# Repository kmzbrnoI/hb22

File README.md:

HB22
====

DCC signal booster

## Features

* Input voltage: track+1V – 35 V **DC**
* Output voltage: 14–25 V DCC
* Maximum output current: 3 A
* Adjustable output voltage
* Stepdown for stabilization (energy-effective)
* No big cooler needed
* Analog current limitation to 3 A
* DCC skew rate limitation
* RailCom support
* Possibility to connect expansion module for integration with railroad-control system
* Current sensing, voltage sensing, temperature sensing
* Short-circuit detection, (configurable) automatic restore after short-circuit

## Available expansion modules

- [MTBbus expansion module](exp-mtb)

## Principles

Main MCU does all safety-critical operations:

* Detection of short-circuit
* Railcom pause insertion

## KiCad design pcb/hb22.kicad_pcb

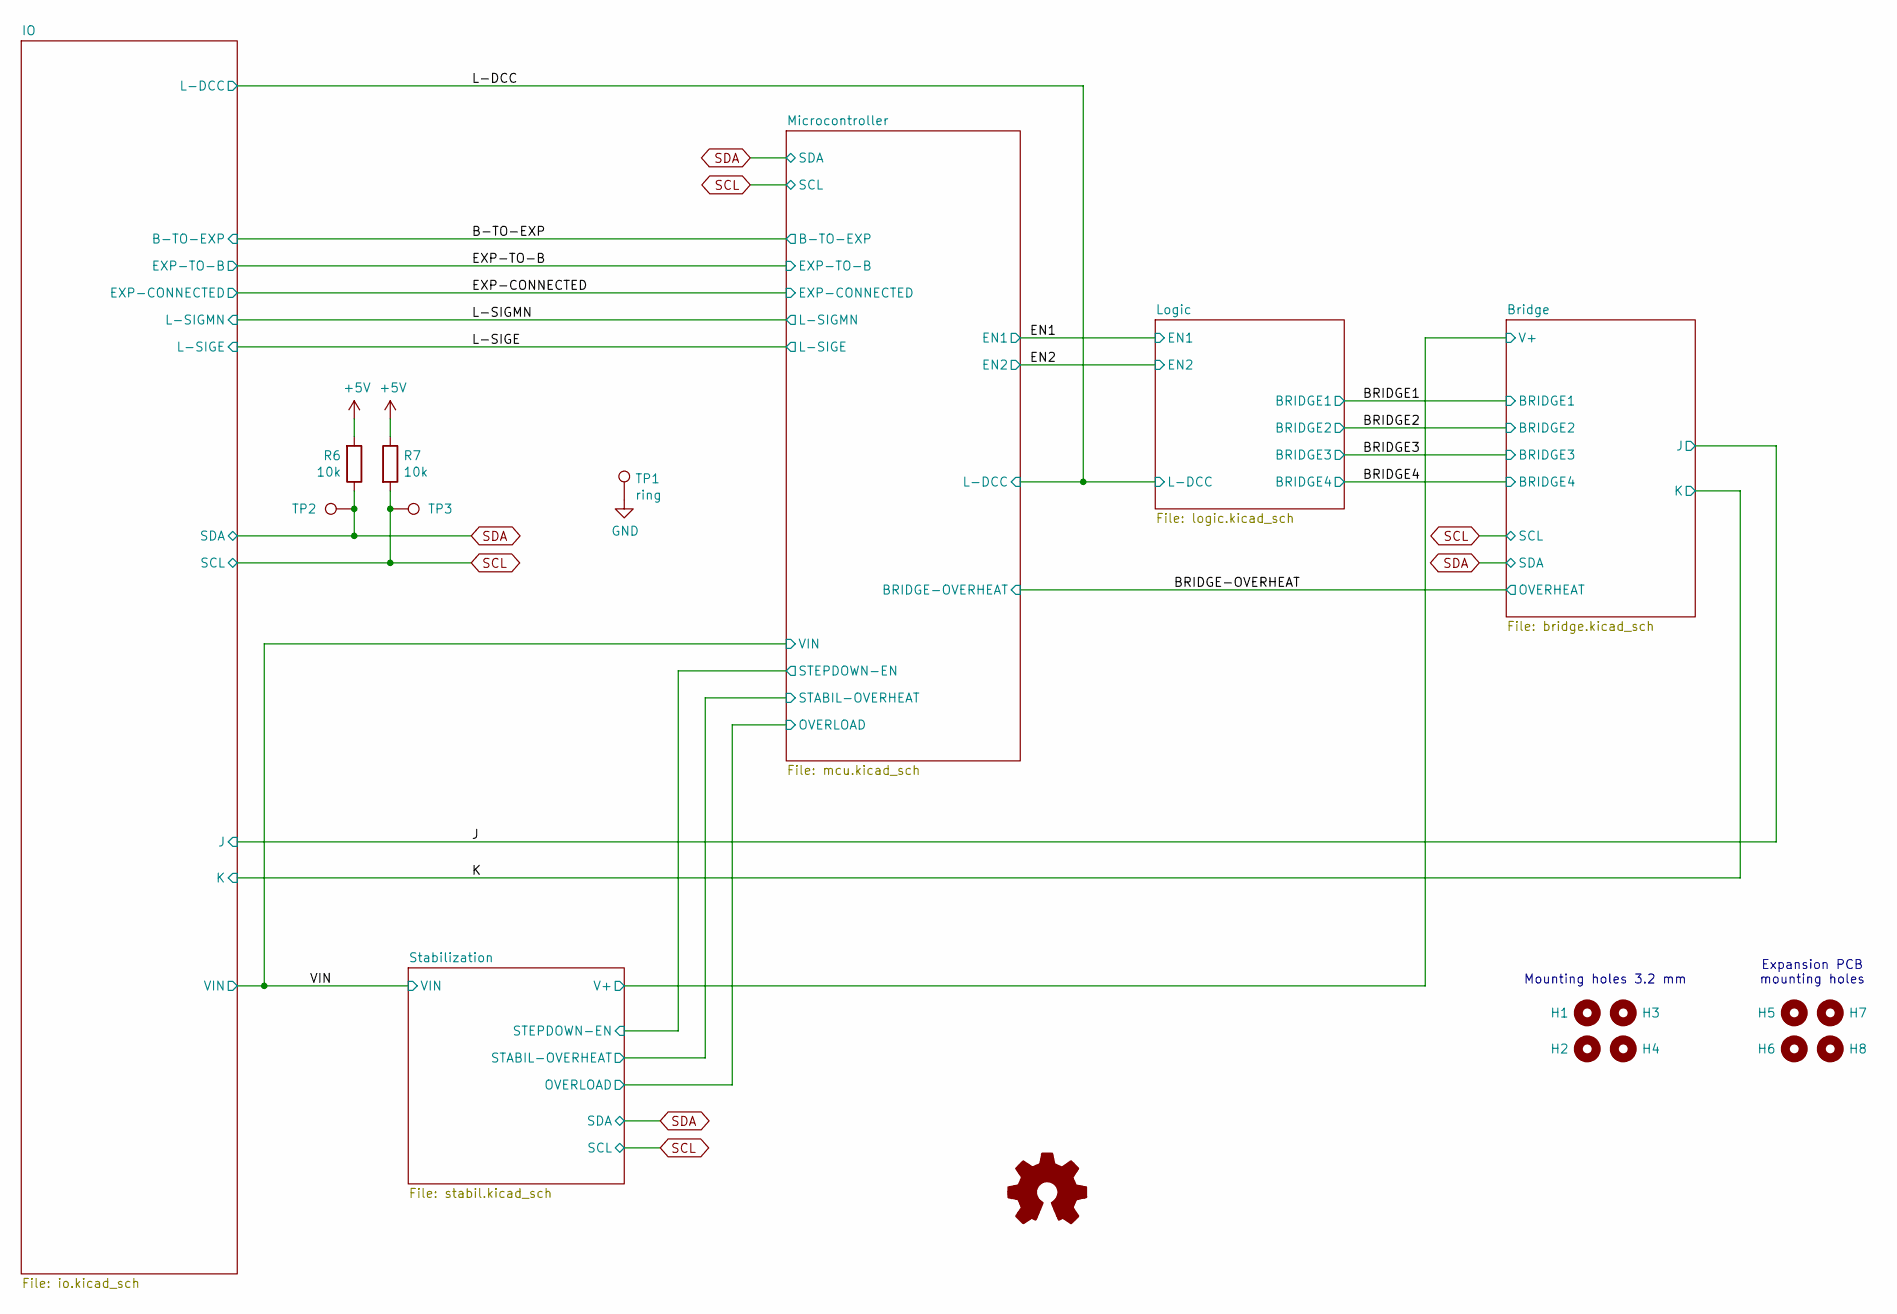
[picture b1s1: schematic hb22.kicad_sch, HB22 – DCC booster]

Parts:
H1, H2, H3, H4, H5, H6, H7, H8: MountingHole_3.2mm_M3_Pad
R6, R7: 10k; R_0805_2012Metric; LCSC C17414
TP1: ring; TestPoint_Loop_D1.80mm_Drill1.0mm_Beaded
TP2, TP3: TestPoint; TestPoint_Pad_D1.0mm

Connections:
+5V: R6.2, R7.1; also elsewhere on the board
GND: TP1.1; also elsewhere on the board
SCL: R7.2, TP3.1; also elsewhere on the board
SDA: R6.1, TP2.1; also elsewhere on the board

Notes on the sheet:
Mounting holes 3.2 mm
Expansion PCB mounting holes

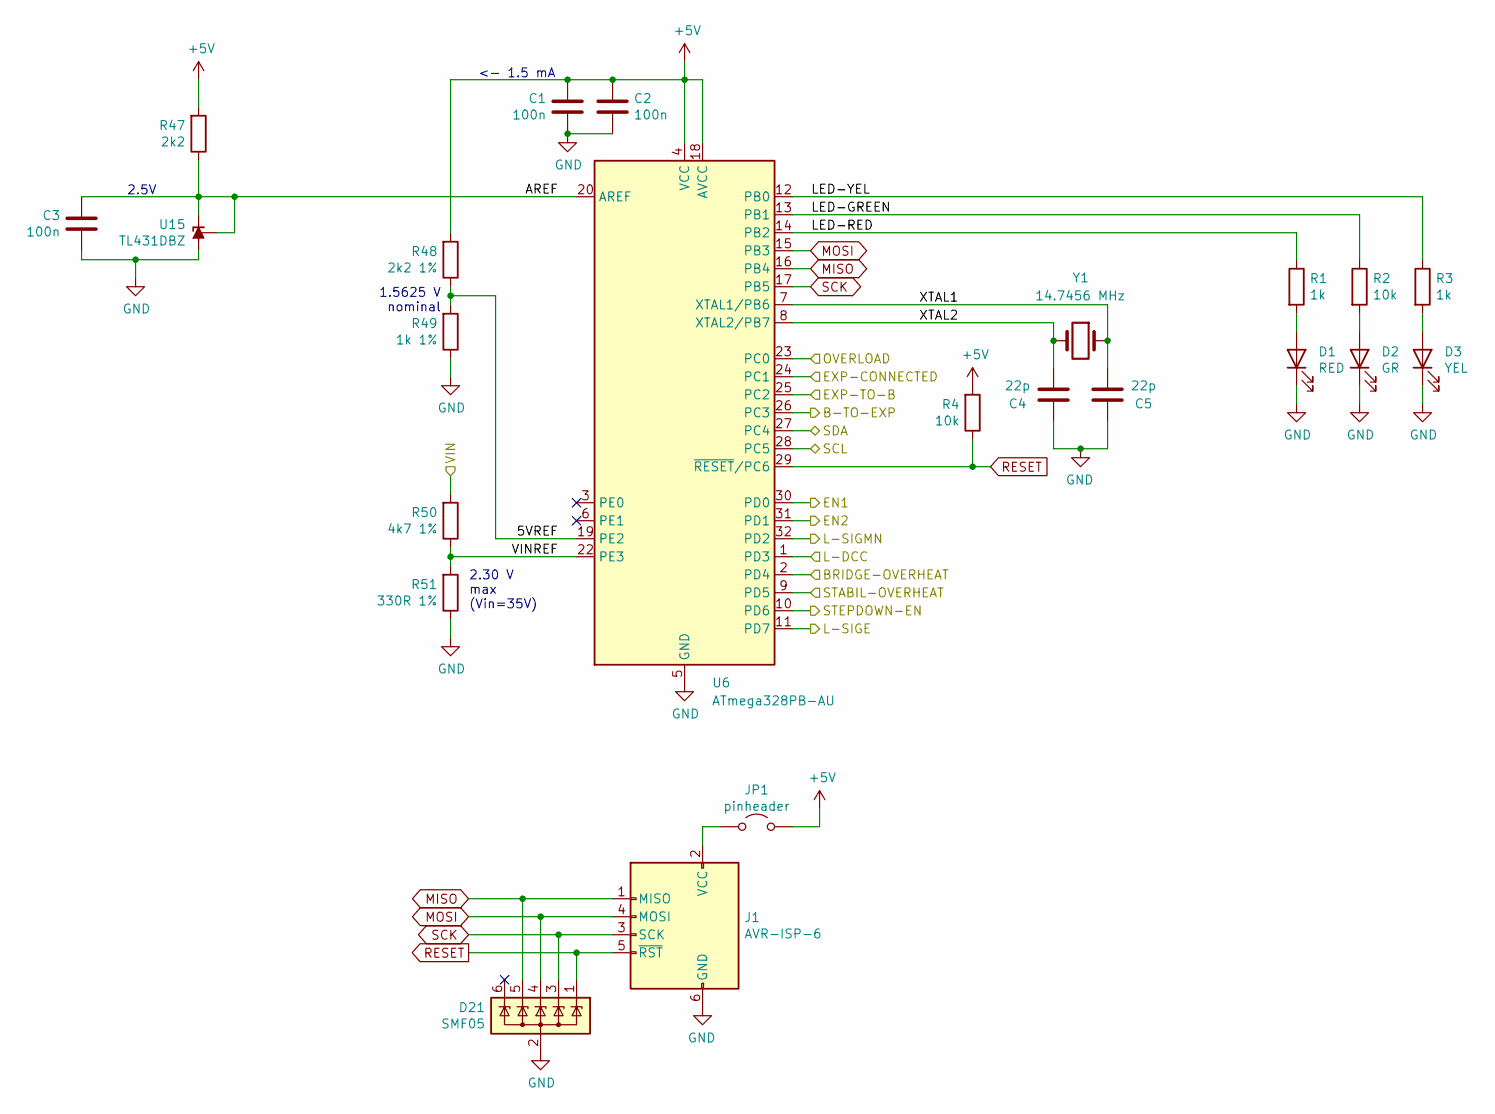
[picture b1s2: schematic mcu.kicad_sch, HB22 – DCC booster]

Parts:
C1, C2, C3: 100n; C_0805_2012Metric; LCSC C49678
C4, C5: 22p; C_0805_2012Metric; LCSC C1804
D1: RED; LED_0805_2012Metric; LCSC C84256
D2: GR; LED_0805_2012Metric; LCSC C2297
D3: YEL; LED_0805_2012Metric; LCSC C2293
D21: SMF05; SOT-363_SC-70-6
J1: AVR-ISP-6; PinHeader_2x03_P2.54mm_Vertical
JP1: pinheader; PinHeader_1x02_P2.54mm_Vertical
R1, R3: 1k; R_0805_2012Metric; LCSC C17513
R2: 10k; R_0805_2012Metric; LCSC C17513
R4: 10k; R_0805_2012Metric; LCSC C17414
R47: 2k2; R_0805_2012Metric
R48: 2k2 1%; R_0805_2012Metric
R49: 1k 1%; R_0805_2012Metric
R50: 4k7 1%; R_0805_2012Metric
R51: 330R 1%; R_0805_2012Metric
U6: ATmega328PB-AU; TQFP-32_7x7mm_P0.8mm
U15: TL431DBZ; SOT-23; LCSC C3113
Y1: 14.7456 MHz; Crystal_SMD_HC49-SD; LCSC C240976

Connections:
+5V: C1.2, C2.1, JP1.1 (A), R4.2, R47.2, R48.2, U6.4 (VCC), U6.18 (AVCC); also elsewhere on the board
/B-TO-EXP: U6.26 (PC3); also elsewhere on the board
/BRIDGE-OVERHEAT: U6.2 (PD4); also elsewhere on the board
/EN1: U6.30 (PD0); also elsewhere on the board
/EN2: U6.31 (PD1); also elsewhere on the board
/EXP-CONNECTED: U6.24 (PC1); also elsewhere on the board
/EXP-TO-B: U6.25 (PC2); also elsewhere on the board
/L-DCC: U6.1 (PD3); also elsewhere on the board
/L-SIGE: U6.11 (PD7); also elsewhere on the board
/L-SIGMN: U6.32 (PD2); also elsewhere on the board
/Microcontroller/5VREF: R48.1, R49.2, U6.19 (PE2)
/Microcontroller/AREF: C3.2, R47.1, U6.20 (AREF), U15.1 (K), U15.2 (REF)
/Microcontroller/LED-GREEN: R2.1, U6.13 (PB1)
/Microcontroller/LED-RED: R1.1, U6.14 (PB2)
/Microcontroller/LED-YEL: R3.1, U6.12 (PB0)
/Microcontroller/OVERLOAD: U6.23 (PC0); also elsewhere on the board
/Microcontroller/STABIL-OVERHEAT: U6.9 (PD5); also elsewhere on the board
/Microcontroller/STEPDOWN-EN: U6.10 (PD6); also elsewhere on the board
/Microcontroller/VINREF: R50.1, R51.2, U6.22 (PE3)
/Microcontroller/XTAL1: C5.1, U6.7 (XTAL1/PB6), Y1.1
/Microcontroller/XTAL2: C4.2, U6.8 (XTAL2/PB7), Y1.2
/VIN: R50.2; also elsewhere on the board
GND: C1.1, C2.2, C3.1, C4.1, C5.2, D1.1 (K), D2.1 (K), D3.1 (K), D21.2 (A), J1.6 (GND), R49.1, R51.1, U6.5 (GND), U6.21 (GND), U15.3 (A); also elsewhere on the board
MISO: D21.5 (K), J1.1 (MISO), U6.16 (PB4)
MOSI: D21.4 (K), J1.4 (MOSI), U6.15 (PB3)
unnamed: D1.2 (A), R1.2
unnamed: D2.2 (A), R2.2
unnamed: D3.2 (A), R3.2
unnamed: J1.2 (VCC), JP1.2 (B)
RESET: D21.1 (K), J1.5 (~RST), R4.1, U6.29 (~RESET/PC6)
SCK: D21.3 (K), J1.3 (SCK), U6.17 (PB5)
SCL: U6.28 (PC5); also elsewhere on the board
SDA: U6.27 (PC4); also elsewhere on the board

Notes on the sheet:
1.5625 V nominal
<- 1.5 mA
2.5V
2.30 V max (Vin=35V)

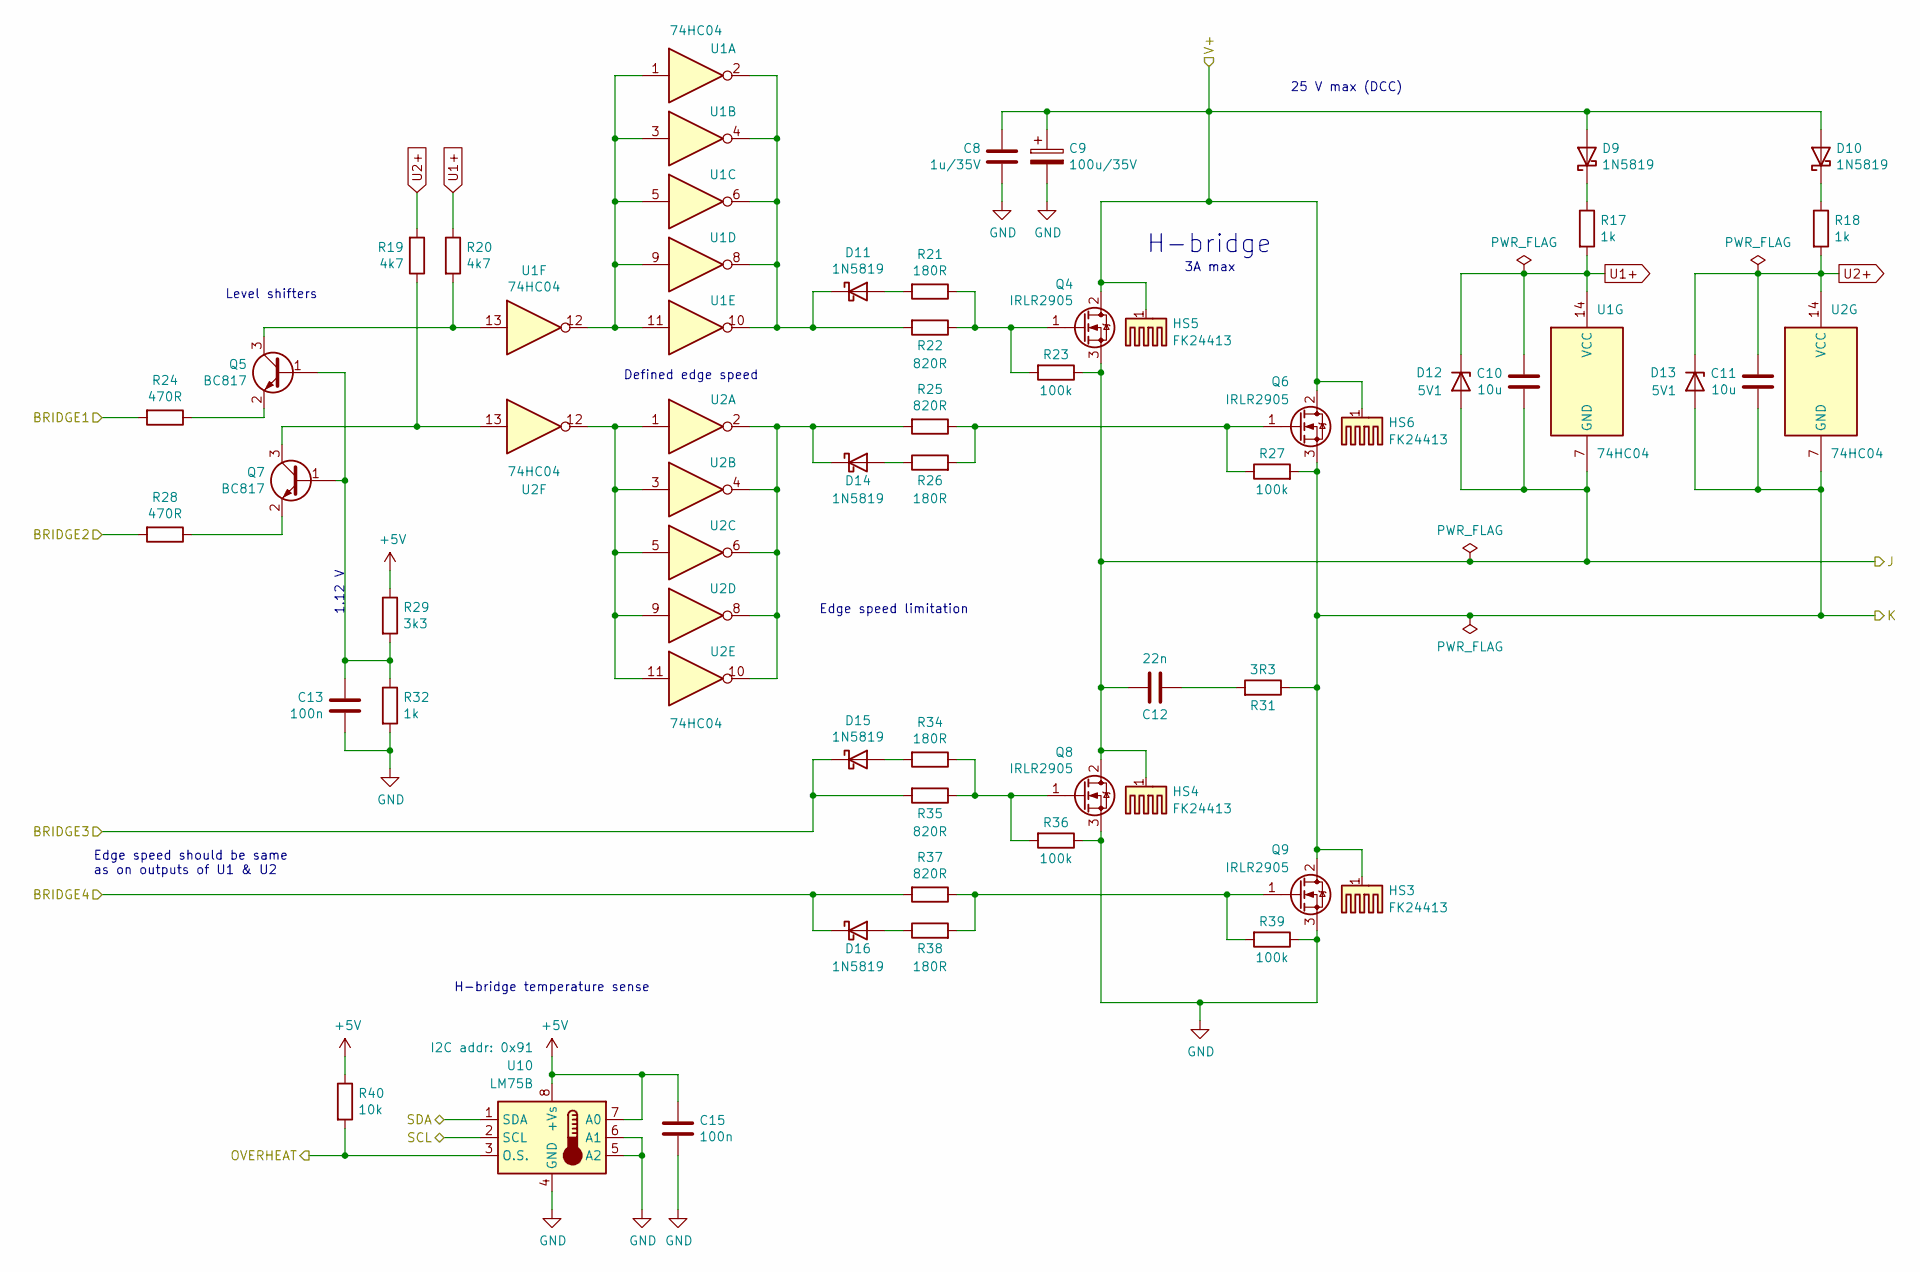
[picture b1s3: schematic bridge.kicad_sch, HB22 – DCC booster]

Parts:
C8: 1u/35V; C_0805_2012Metric
C9: 100u/35V; CP_Radial_D6.3mm_P2.50mm
C10, C11: 10u; C_0805_2012Metric
C12: 22n; C_0805_2012Metric
C13, C15: 100n; C_0805_2012Metric
D9, D10, D11, D14, D15, D16: 1N5819; D_SOD-123
D12, D13: 5V1; SOT-23
HS3, HS4, HS5, HS6: FK24413; Heatsink_Fischer_FK24413DPAK_23x13mm
Q4, Q6, Q8, Q9: IRLR2905; TO-252-2
Q5, Q7: BC817; SOT-23
R17, R18: 1k; R_2512_6332Metric
R19, R20: 4k7; R_0805_2012Metric
R21, R26, R34, R38: 180R; R_0805_2012Metric
R22, R25, R35, R37: 820R; R_0805_2012Metric
R23, R27, R36, R39: 100k; R_0805_2012Metric
R24, R28: 470R; R_0805_2012Metric
R29: 3k3; R_0805_2012Metric
R31: 3R3; R_0805_2012Metric
R32: 1k; R_0805_2012Metric
R40: 10k; R_0805_2012Metric
U1, U2: 74HC04; DIP-14_W8.89mm_SMDSocket_LongPads
U10: LM75B; SOIC-8_3.9x4.9mm_P1.27mm

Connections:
+5V: C15.1, R29.1, R40.1, U10.7 (A0), U10.8 (+Vs); also elsewhere on the board
/BRIDGE1: R24.2; also elsewhere on the board
/BRIDGE2: R28.2; also elsewhere on the board
/BRIDGE3: D15.1 (K), R35.2; also elsewhere on the board
/BRIDGE4: D16.1 (K), R37.2; also elsewhere on the board
/BRIDGE-OVERHEAT: R40.2, U10.3 (O.S.); also elsewhere on the board
/Bridge/V+: C8.2, C9.1, D9.2 (A), D10.2 (A), HS5.1, HS6.1, Q4.2 (D), Q6.2 (D); also elsewhere on the board
/J: C10.1, C12.2, D12.1 (A), HS4.1, Q4.3 (S), Q8.2 (D), R23.1, U1.7 (GND); also elsewhere on the board
/K: C11.1, D13.1 (A), HS3.1, Q6.3 (S), Q9.2 (D), R27.2, R31.1, U2.7 (GND); also elsewhere on the board
GND: C8.1, C9.2, C13.1, C15.2, Q8.3 (S), Q9.3 (S), R32.2, R36.1, R39.1, U10.4 (GND), U10.5 (A2), U10.6 (A1); also elsewhere on the board
unnamed: C12.1, R31.2
unnamed: D9.1 (K), R17.1
unnamed: D10.1 (K), R18.1
unnamed: D11.2 (A), R21.2
unnamed: D11.1 (K), R22.2, U1.2, U1.4, U1.6, U1.8, U1.10
unnamed: D14.2 (A), R26.1
unnamed: D14.1 (K), R25.2, U2.2, U2.4, U2.6, U2.8, U2.10
unnamed: D15.2 (A), R34.2
unnamed: D16.2 (A), R38.1
unnamed: Q4.1 (G), R21.1, R22.1, R23.2
unnamed: C13.2, Q5.1 (B), Q7.1 (B), R29.2, R32.1
unnamed: Q5.3 (C), R20.2, U1.13
unnamed: Q5.2 (E), R24.1
unnamed: Q6.1 (G), R25.1, R26.2, R27.1
unnamed: Q7.3 (C), R19.1, U2.13
unnamed: Q7.2 (E), R28.1
unnamed: Q8.1 (G), R34.1, R35.1, R36.2
unnamed: Q9.1 (G), R37.1, R38.2, R39.2
unnamed: U1.1, U1.3, U1.5, U1.9, U1.11, U1.12
unnamed: U2.1, U2.3, U2.5, U2.9, U2.11, U2.12
SCL: U10.2 (SCL); also elsewhere on the board
SDA: U10.1 (SDA); also elsewhere on the board
U1+: C10.2, D12.3 (K), R17.2, R20.1, U1.14 (VCC)
U2+: C11.2, D13.3 (K), R18.2, R19.2, U2.14 (VCC)

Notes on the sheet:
25 V max (DCC)
3A max
1.12 V
H-bridge
Defined edge speed
Edge speed should be same as on outputs of U1 & U2
Edge speed limitation
H-bridge temperature sense
Level shifters

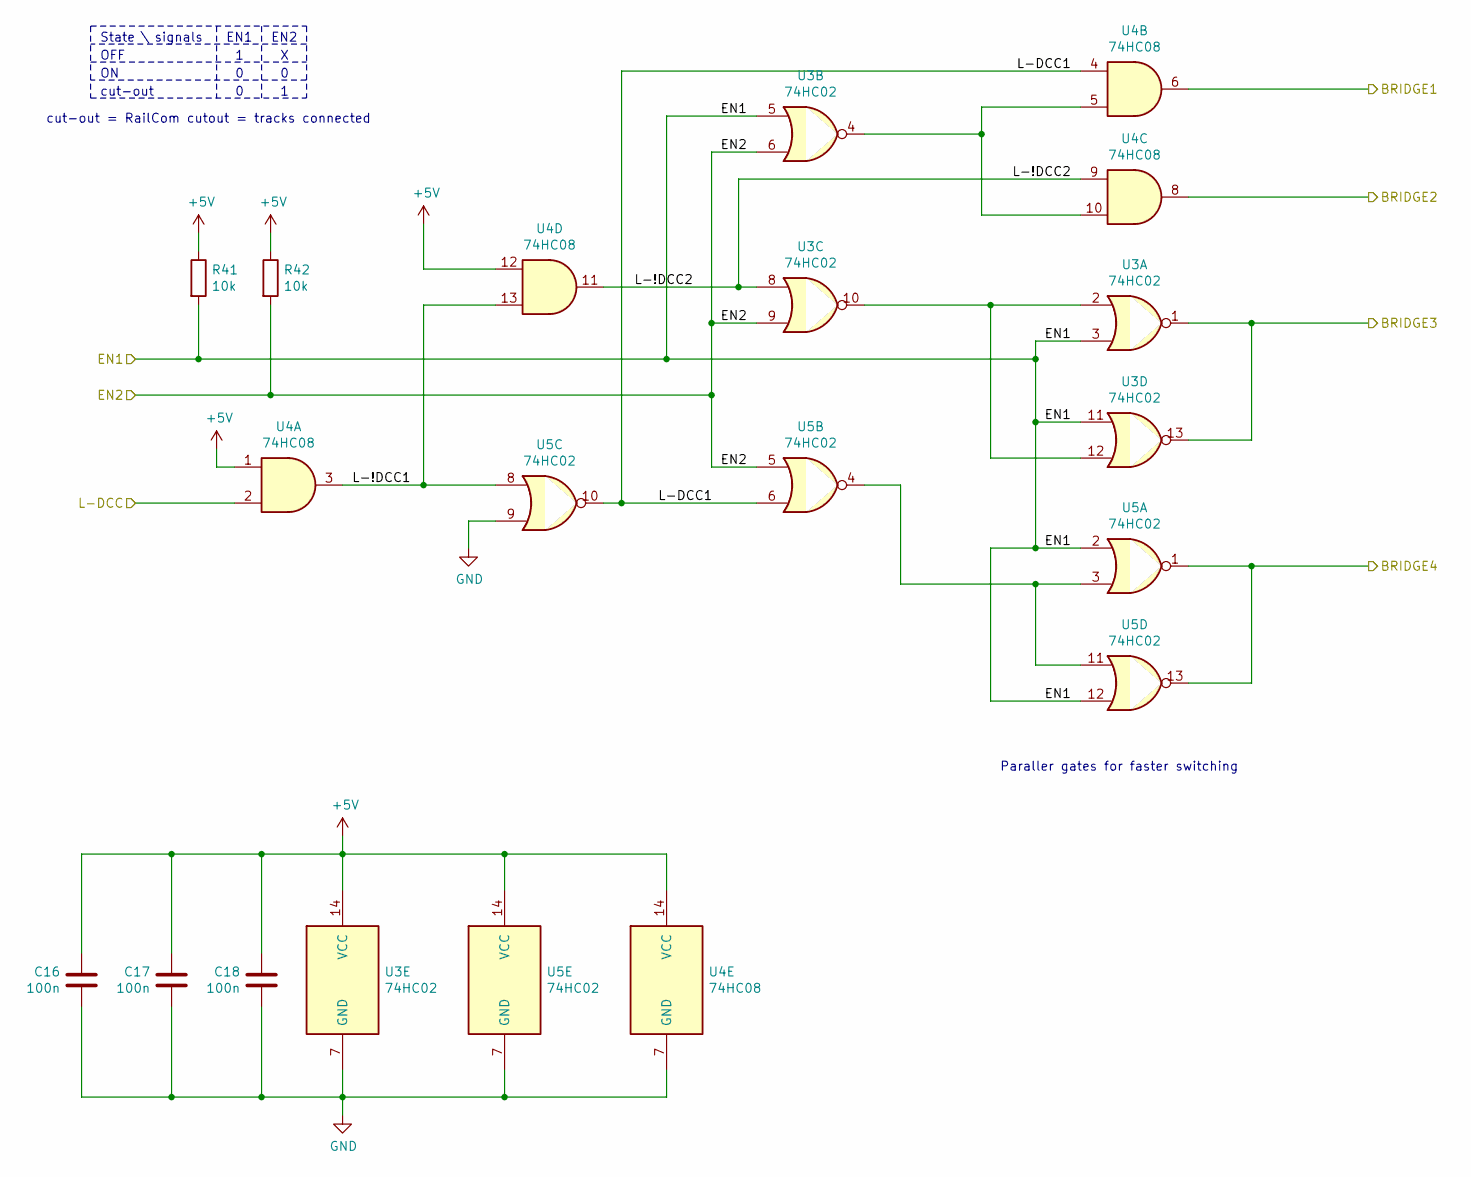
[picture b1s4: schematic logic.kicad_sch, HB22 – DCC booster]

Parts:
C16, C17, C18: 100n; C_0805_2012Metric
R41, R42: 10k; R_0805_2012Metric
U3, U5: 74HC02; DIP-14_W8.89mm_SMDSocket_LongPads
U4: 74HC08; DIP-14_W8.89mm_SMDSocket_LongPads

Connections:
+5V: C16.2, C17.2, C18.2, R41.1, R42.1, U3.14 (VCC), U4.1, U4.12, U4.14 (VCC), U5.14 (VCC); also elsewhere on the board
/BRIDGE1: U4.6; also elsewhere on the board
/BRIDGE2: U4.8; also elsewhere on the board
/BRIDGE3: U3.1, U3.13; also elsewhere on the board
/BRIDGE4: U5.1, U5.13; also elsewhere on the board
/EN1: R41.2, U3.3, U3.5, U3.11, U5.2, U5.12; also elsewhere on the board
/EN2: R42.2, U3.6, U3.9, U5.5; also elsewhere on the board
/L-DCC: U4.2; also elsewhere on the board
/Logic/L-!DCC1: U4.3, U4.13, U5.8
/Logic/L-!DCC2: U3.8, U4.9, U4.11
/Logic/L-DCC1: U4.4, U5.6, U5.10
GND: C16.1, C17.1, C18.1, U3.7 (GND), U4.7 (GND), U5.7 (GND), U5.9; also elsewhere on the board
unnamed: U3.4, U4.5, U4.10
unnamed: U3.2, U3.10, U3.12
unnamed: U5.3, U5.4, U5.11

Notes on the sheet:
EN2
State \ signals
OFF
Paraller gates for faster switching
cut-out = RailCom cutout = tracks connected
cut-out
EN1

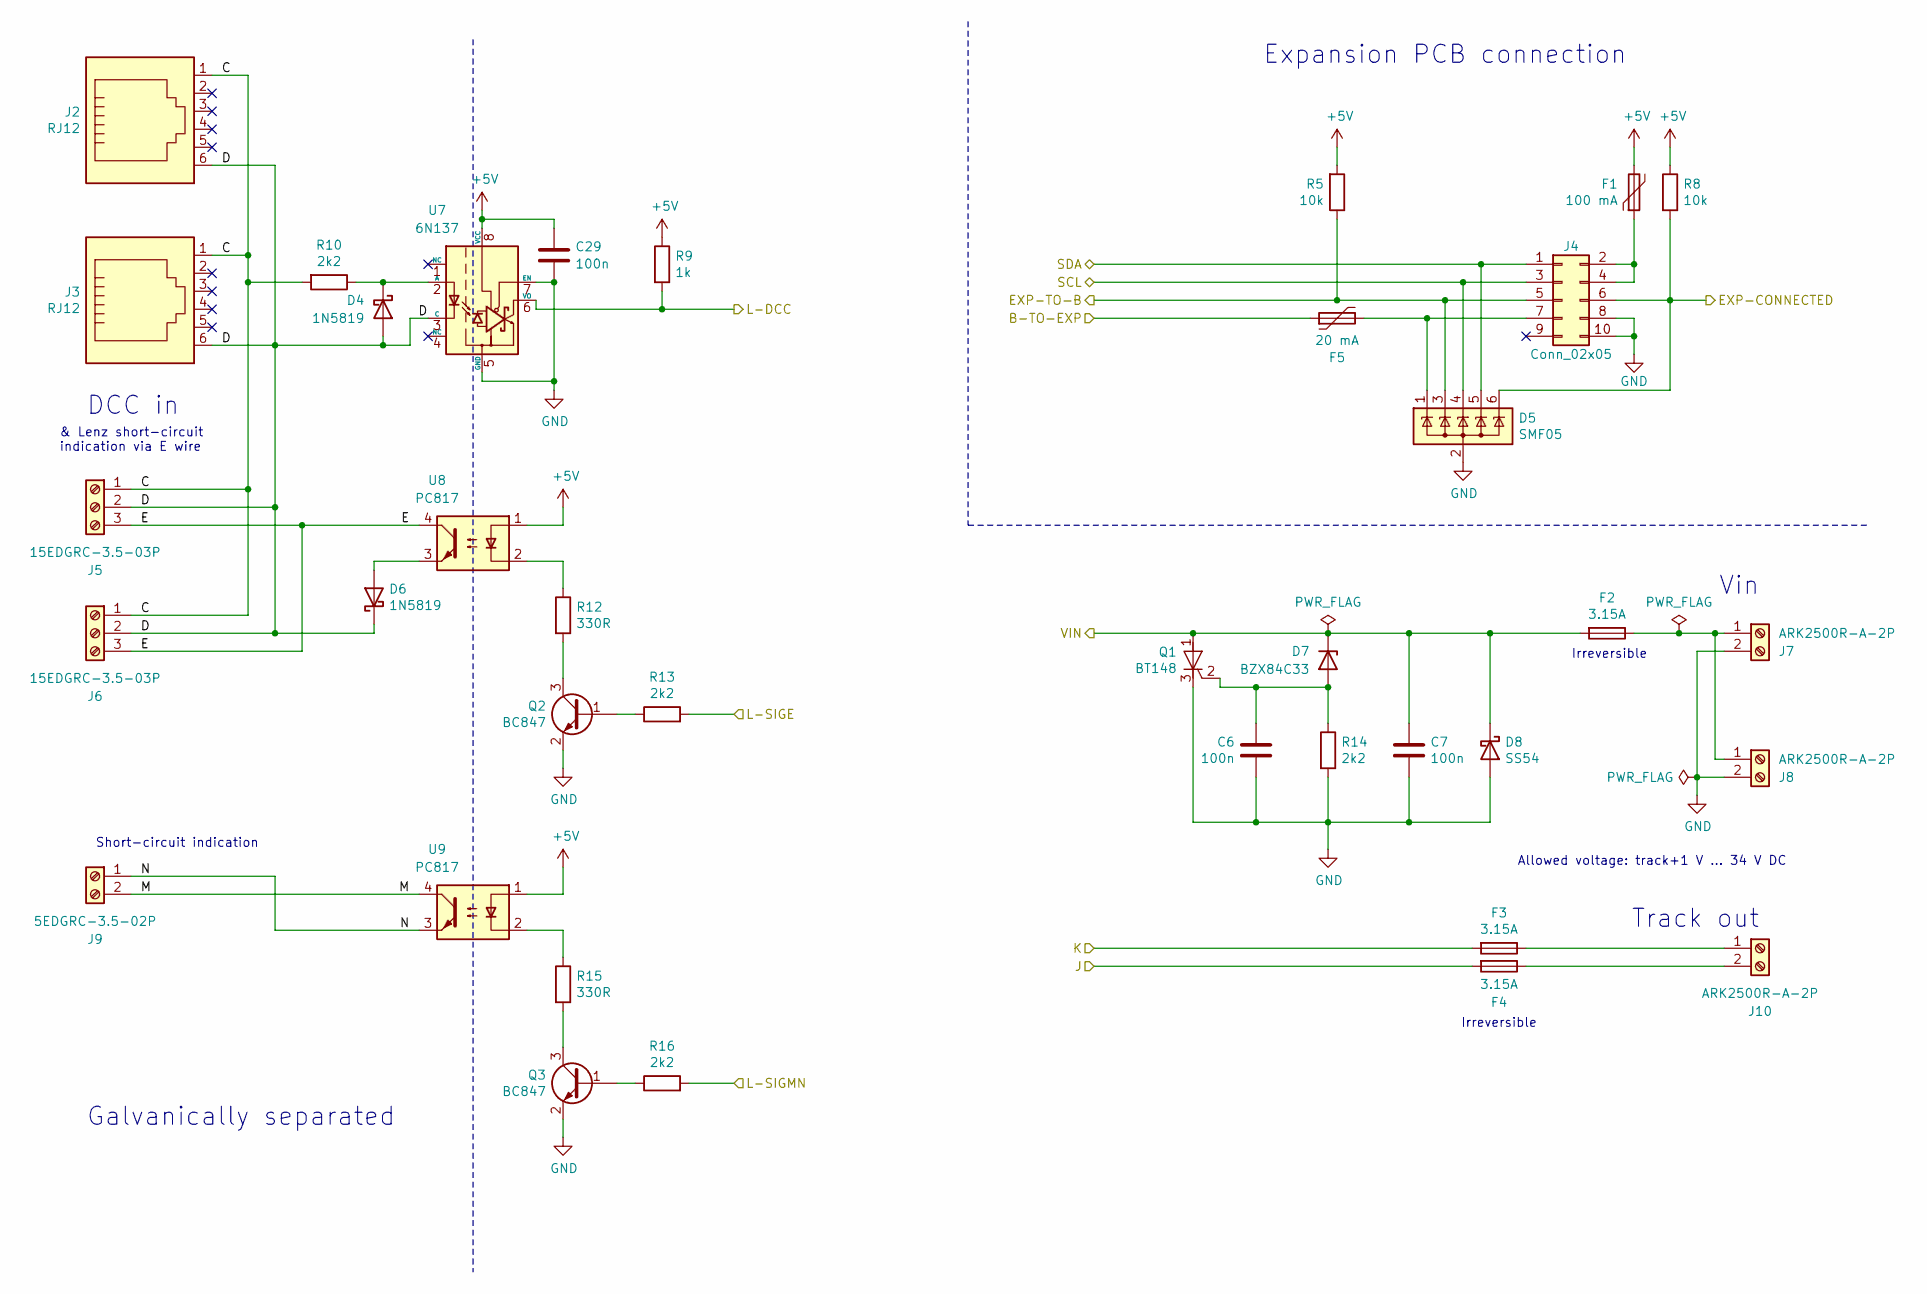
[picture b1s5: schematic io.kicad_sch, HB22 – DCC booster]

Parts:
C6, C7, C29: 100n; C_0805_2012Metric
D4, D6: 1N5819; D_SOD-123
D5: SMF05; SOT-363_SC-70-6
D7: BZX84C33; SOT-23
D8: SS54; D_SMA
F1: 100 mA; Fuse_1206_3216Metric
F2, F3, F4: 3.15A; Fuseholder_Cylinder-5x20mm_Stelvio-Kontek_PTF78_Horizontal_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
F5: 20 mA; Fuse_1206_3216Metric
J2, J3: RJ12; RJ25_Wayconn_MJEA-660X1_Horizontal
J4: Conn_02x05; PinSocket_2x05_P2.54mm_Vertical
J5, J6: 15EDGRC-3.5-03P; PhoenixContact_MC_1,5_3-G-3.5_1x03_P3.50mm_Horizontal
J7, J8, J10: ARK2500R-A-2P; PhoenixContact_MSTBA_2,5_2-G_1x02_P5.00mm_Horizontal
J9: 5EDGRC-3.5-02P; PhoenixContact_MC_1,5_2-G-3.5_1x02_P3.50mm_Horizontal
Q1: BT148; SOT-223
Q2, Q3: BC847; SOT-23
R5: 10k; R_0805_2012Metric; LCSC C17414
R8: 10k; R_0805_2012Metric
R9: 1k; R_0805_2012Metric
R10, R13, R14, R16: 2k2; R_0805_2012Metric
R12, R15: 330R; R_0805_2012Metric
U7: 6N137; DIP-8_W8.89mm_SMDSocket_LongPads
U8, U9: PC817; DIP-4_W8.89mm_SMDSocket_LongPads

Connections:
+5V: C29.1, F1.2, R5.2, R8.1, R9.1, U7.8 (VCC), U8.1, U9.1; also elsewhere on the board
/B-TO-EXP: F5.1; also elsewhere on the board
/EXP-CONNECTED: D5.6 (K), J4.6, R8.2; also elsewhere on the board
/EXP-TO-B: D5.3 (K), J4.5, R5.1; also elsewhere on the board
/IO/C: J2.1, J3.1, J5.1, J6.1, R10.2
/IO/D: D4.2 (A), D6.1 (K), J2.6, J3.6, J5.2, J6.2, U7.3 (C)
/IO/E: J5.3, J6.3, U8.4
/IO/M: J9.2, U9.4
/IO/N: J9.1, U9.3
/J: F4.2; also elsewhere on the board
/K: F3.2; also elsewhere on the board
/L-DCC: R9.2, U7.6 (VO); also elsewhere on the board
/L-SIGE: R13.2; also elsewhere on the board
/L-SIGMN: R16.2; also elsewhere on the board
/VIN: C7.1, D7.3 (K), D8.1 (K), F2.2, Q1.1 (A); also elsewhere on the board
GND: C6.1, C7.2, C29.2, D5.2 (A), D8.2 (A), J4.8, J4.10, J7.2, J8.2, Q1.3 (K), Q2.2 (E), Q3.2 (E), R14.2, U7.5 (GND), U7.7 (EN); also elsewhere on the board
unnamed: D4.1 (K), R10.1, U7.2 (A)
unnamed: D6.2 (A), U8.3
unnamed: C6.2, D7.1 (A), Q1.2 (G), R14.1
unnamed: F1.1, J4.2, J4.4
unnamed: D5.1 (K), F5.2, J4.7
unnamed: F2.1, J7.1, J8.1
unnamed: F3.1, J10.1
unnamed: F4.1, J10.2
unnamed: Q2.1 (B), R13.1
unnamed: Q2.3 (C), R12.2
unnamed: Q3.1 (B), R16.1
unnamed: Q3.3 (C), R15.2
unnamed: R12.1, U8.2
unnamed: R15.1, U9.2
SCL: D5.4 (K), J4.3; also elsewhere on the board
SDA: D5.5 (K), J4.1; also elsewhere on the board

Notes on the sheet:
Allowed voltage: track+1 V ... 34 V DC
Irreversible
Vin
& Lenz short-circuit indication via E wire
Galvanically separated
Track out
Expansion PCB connection
Short-circuit indication
DCC in

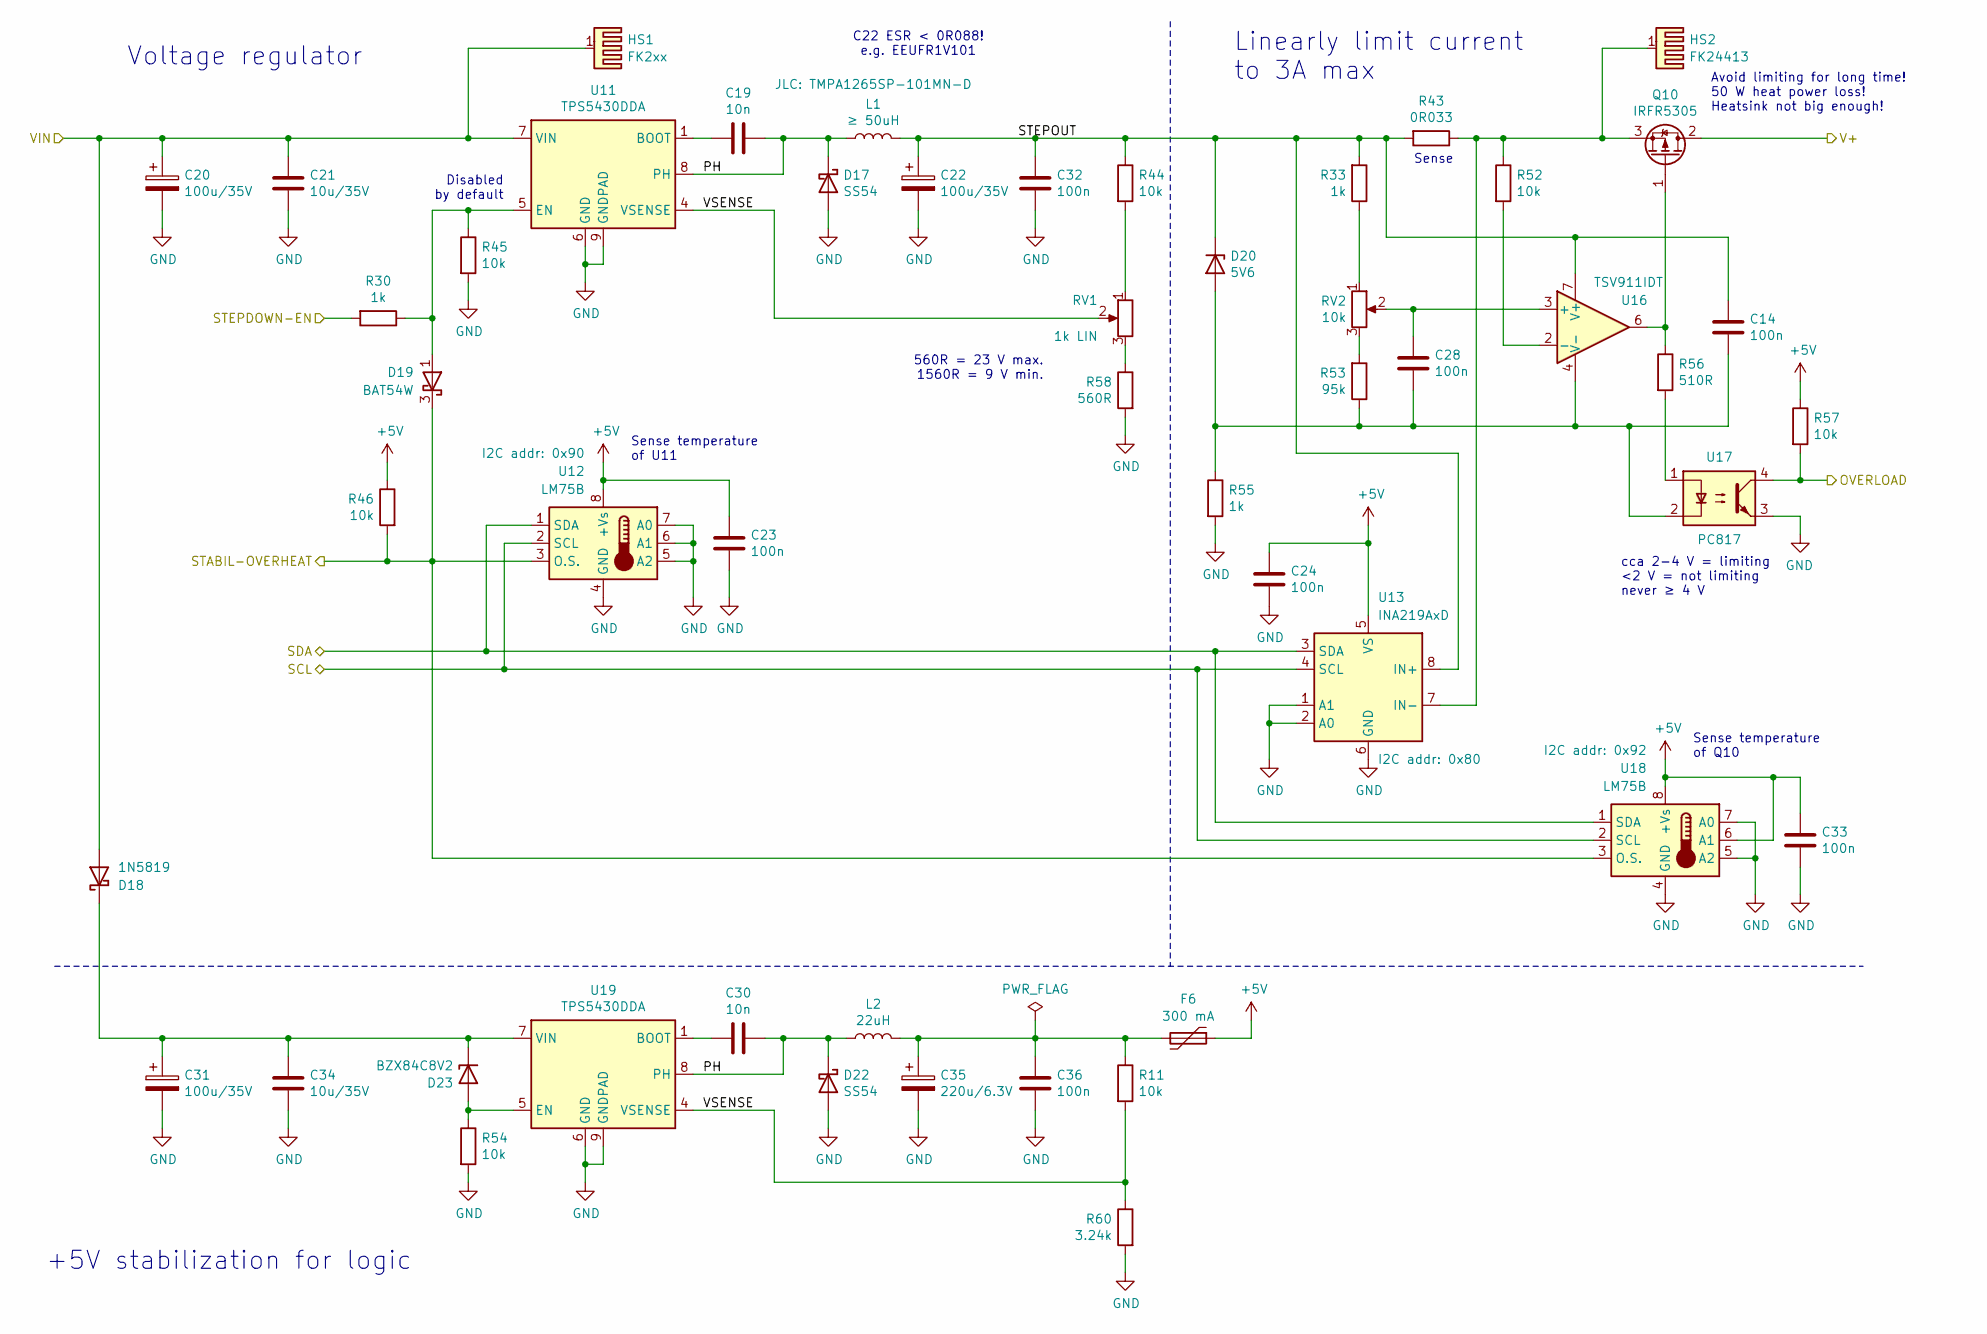
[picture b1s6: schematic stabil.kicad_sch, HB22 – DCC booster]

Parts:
C14, C23, C24, C28, C32, C33, C36: 100n; C_0805_2012Metric
C19, C30: 10n; C_0805_2012Metric
C20, C31: 100u/35V; CP_Radial_D6.3mm_P2.50mm
C21, C34: 10u/35V; C_0805_2012Metric
C22: 100u/35V; CP_Radial_D8.0mm_P3.50mm
C35: 220u/6.3V; CP_Radial_D8.0mm_P3.50mm
D17, D22: SS54; D_SMA
D18: 1N5819; D_SOD-123
D19: BAT54W; SOT-323_SC-70
D20: 5V6; SOT-23
D23: BZX84C8V2; SOT-23
F6: 300 mA; Fuse_2920_7451Metric
HS1: FK2xx; Heatsink_Fischer_FK24413DPAK_23x13mm
HS2: FK24413; Heatsink_Fischer_FK24413DPAK_23x13mm
L1: ≥ 50uH; L_TaiTech_TMPC1265_13.5x12.5mm; JLC TMPA1265SP-101MN-D
L2: 22uH; L_Changjiang_FNR4020S
Q10: IRFR5305; TO-252-2
R11, R44, R45, R46, R52, R54, R57: 10k; R_0805_2012Metric
R30, R33: 1k; R_0805_2012Metric
R43: 0R033; R_2512_6332Metric
R53: 95k; R_0805_2012Metric
R55: 1k; R_2512_6332Metric
R56: 510R; R_0805_2012Metric
R58: 560R; R_0805_2012Metric
R60: 3.24k; R_0805_2012Metric
RV1: 1k LIN; Potentiometer_Piher_PT-6-V_Vertical
RV2: 10k; Potentiometer_Piher_PT-6-V_Vertical
U11, U19: TPS5430DDA; TI_SO-PowerPAD-8_ThermalVias
U12, U18: LM75B; SOIC-8_3.9x4.9mm_P1.27mm
U13: INA219AxD; SOIC-8_3.9x4.9mm_P1.27mm
U16: TSV911IDT; SOIC-8_3.9x4.9mm_P1.27mm
U17: PC817; DIP-4_W8.89mm_SMDSocket_LongPads

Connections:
+5V: C23.1, C24.1, C33.1, F6.1, R46.1, R57.1, U12.8 (+Vs), U13.5 (VS), U18.6 (A1), U18.8 (+Vs); also elsewhere on the board
/Bridge/V+: Q10.2 (D); also elsewhere on the board
/Microcontroller/OVERLOAD: R57.2, U17.4; also elsewhere on the board
/Microcontroller/STABIL-OVERHEAT: D19.3 (K), R46.2, U12.3 (O.S.), U18.3 (O.S.); also elsewhere on the board
/Microcontroller/STEPDOWN-EN: R30.2; also elsewhere on the board
/Stabilization/PH: C19.1, C30.1, D17.1 (K), D22.1 (K), L1.1, L2.1, U11.8 (PH), U19.8 (PH)
/Stabilization/STEPOUT: C14.1, C22.1, C32.1, D20.3 (K), L1.2, R33.2, R43.2, R44.1, U13.8 (IN+), U16.7 (V+)
/Stabilization/VSENSE: R11.2, R60.1, RV1.2, U11.4 (VSENSE), U19.4 (VSENSE)
/VIN: C20.1, C21.1, D18.2 (A), HS1.1, U11.7 (VIN); also elsewhere on the board
GND: C20.2, C21.2, C22.2, C23.2, C24.2, C31.2, C32.2, C33.2, C34.2, C35.2, C36.2, D17.2 (A), D22.2 (A), R45.2, R54.2, R55.2, R58.2, R60.2, U11.6 (GND), U11.9 (GNDPAD), U12.4 (GND), U12.5 (A2), U12.6 (A1), U12.7 (A0), U13.1 (A1), U13.2 (A0), U13.6 (GND), U17.3, U18.4 (GND), U18.5 (A2), U18.7 (A0), U19.6 (GND), U19.9 (GNDPAD); also elsewhere on the board
unnamed: C35.1, C36.1, F6.2, L2.2, R11.1
unnamed: C31.1, C34.1, D18.1 (K), D23.3 (K), U19.7 (VIN)
unnamed: D19.1 (A), R30.1, R45.1, U11.5 (EN)
unnamed: C14.2, C28.2, D20.1 (A), R53.1, R55.1, U16.4 (V-), U17.2
unnamed: D23.1 (A), R54.1, U19.5 (EN)
unnamed: Q10.1 (G), R56.1, U16.6
unnamed: HS2.1, Q10.3 (S), R43.1, R52.1, U13.7 (IN-)
unnamed: R33.1, RV2.1
unnamed: R44.2, RV1.1
unnamed: R53.2, RV2.3
unnamed: R56.2, U17.1
unnamed: R58.1, RV1.3
unnamed: C19.2, U11.1 (BOOT)
unnamed: C28.1, RV2.2, U16.3 (+)
unnamed: R52.2, U16.2 (-)
unnamed: C30.2, U19.1 (BOOT)
SCL: U12.2 (SCL), U13.4 (SCL), U18.2 (SCL); also elsewhere on the board
SDA: U12.1 (SDA), U13.3 (SDA), U18.1 (SDA); also elsewhere on the board

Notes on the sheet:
Avoid limiting for long time! 50 W heat power loss! Heatsink not big enough!
560R = 23 V max. 1560R = 9 V min.
C22 ESR < 0R088! e.g. EEUFR1V101
Sense temperature of U11
Voltage regulator
cca 2-4 V = limiting <2 V = not limiting never ≥ 4 V
Disabled by default
+5V stabilization for logic
Sense
Sense temperature of Q10
Linearly limit current to 3A max

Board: 4 copper layers, 182 parts (0 on the bottom side), 106 nets, no tracks yet.

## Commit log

2021-12-28 Add empty KiCad project.
2021-12-28 Add MTB expansion PCB schematics.
2021-12-28 Add descripton etc.
2021-12-28 MTB EXP: add GPIOs between booster & expander.
2021-12-28 MTB EXP: annotate schematics, ERC clean.
2021-12-28 Add LCSC numbers.
2021-12-28 MTB exp: add testpads.
2021-12-28 Add mountingholes.
2021-12-29 Add MCU ATmega, add expansion connector.
2021-12-31 Add H bridge.
2022-01-01 Add logic schematics.
2022-01-01 Add IO schematics.
2022-01-01 Vin & Vout: add protections.
2022-01-01 Add stabilization schematics (5V + stepdown).
2022-01-01 Add INA219 & LM75B.
2022-01-01 EXP-MTB: add 6N137 pull-ups.
2022-01-01 onnect hierarchical schematics in root schematic.
2022-01-03 Add Vin & 5 V measurements.
2022-01-03 Bridge: use single voltage reference.
2022-01-08 Move i2c pullups to main schematics.
2022-01-08 First round of footprint annotations.
2022-01-09 Connect temperature sensor to stepdown enable.
    Add hardware overcurrent protection (independent on MCU).
2022-01-09 Bridge: change transistors (too high Rds).
2022-01-09 Add first version of linear limiter.
2022-01-09 Add overload indication to MCU.
2022-01-10 EXP-MTB: add MCU "active" pin.
2022-01-10 EXP-MTB: ad missing 100n capacitor to 75176.
2022-01-10 EXP-MTB: add protection resistor.
2022-01-10 Stepdown: hardware limit output voltage to 9V-25 V.
2022-01-11 Add testcases.
2022-01-11 Add README.
2022-01-11 Add programming connector TVS protection.
2022-01-11 Tests: add ESD.
2022-01-11 Change divider to set maximum stepdown voltage to 23 V.
2022-01-21 Migrate to KiCad 6.
2025-02-20 Update to KiCad 8.
2025-02-20 Remove misplaced wires.
2025-02-20 Tweak exapander connector.
2025-02-20 Use 1N5819 instead of 1N4148.
2025-02-20 gitignore: add *.lck.
2025-02-20 Export root page escription to other pages.
2025-02-21 Add capacitor to U7, fix new parts.
2025-02-21 Use normal SMD footprints, avoid handsolder.
2025-02-21 Add stabil heatsinks, minor improvements.
2025-02-21 Add temp. sensor for current limiter.
2025-02-21 Add heasinks to output bridge.
2025-02-22 Specify screw terminals, add footprints.
2025-02-22 Migrate exp-mtb to KiCad 8.
2025-02-22 exp-mtb: move pcb to 'pcb' directory.
2025-02-22 exp-mtb: remove address jumpers.
    Address will be set in EEPROM.
2025-02-22 Use polyfuse instead of resistor for main-exp protection.
    Make voltage measurement possible.
2025-02-22 exp-mtb: use 78M05 instead of 78L05.
    75176 can draw quite high current.
2025-02-22 exp-mtb: use standard SMD packages, no handsolder.
2025-02-23 Bridge: use IRLR2905 transistors instead of IRFR4105.
    IRFR4105 seem not to be available.
2025-02-23 Add F5 missing footprint.
2025-02-26 Use switched power supply for 5V internal.
    78M05 would have 2.5 W of heat loss on it @ 30V input.
    Other minor improvements.
2025-02-26 Change pages order.
2025-02-27 Use ATmega328pb instead of ATmega328p.
    Reason: obtain some free pins as a reserve.
2025-12-25 Add exp-mtb readme.

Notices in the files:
pcb/bridge.kicad_sch:
https://creativecommons.org/licenses/by-sa/4.0
Released under the Creative Commons Attribution-ShareAlike 4.0 License
